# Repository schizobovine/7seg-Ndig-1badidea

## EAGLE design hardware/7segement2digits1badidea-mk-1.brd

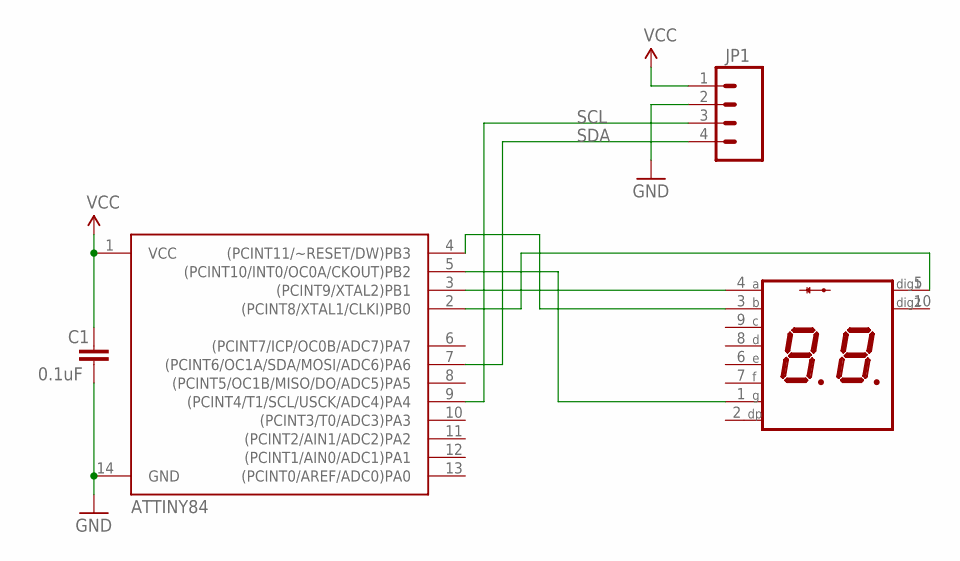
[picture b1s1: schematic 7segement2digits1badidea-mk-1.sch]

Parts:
C1: 0.1uF; CAP-PTH-SMALL
JP1: M04PTH; 1X04
U$1: 7SEG_2DIG_CA; 7SEG_2DIG_FUCKYOU
U$2: ATTINY84; SO14

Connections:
GND: C1.2, JP1.2, U$2.14 (GND)
unnamed: U$1.5 (DIG1), U$2.2 ((PCINT8/XTAL1/CLKI)PB0)
unnamed: U$1.4 (A), U$2.3 ((PCINT9/XTAL2)PB1)
unnamed: U$1.3 (B), U$2.4 ((PCINT11/~RESET/DW)PB3)
unnamed: U$1.1 (G), U$2.5 ((PCINT10/INT0/OC0A/CKOUT)PB2)
SCL: JP1.3, U$2.9 ((PCINT4/T1/SCL/USCK/ADC4)PA4)
SDA: JP1.4, U$2.7 ((PCINT6/OC1A/SDA/MOSI/ADC6)PA6)
VCC: C1.1, JP1.1, U$2.1 (VCC)

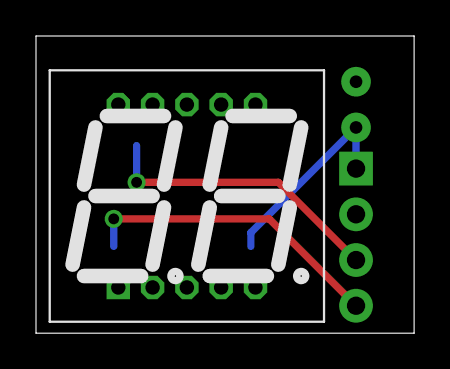
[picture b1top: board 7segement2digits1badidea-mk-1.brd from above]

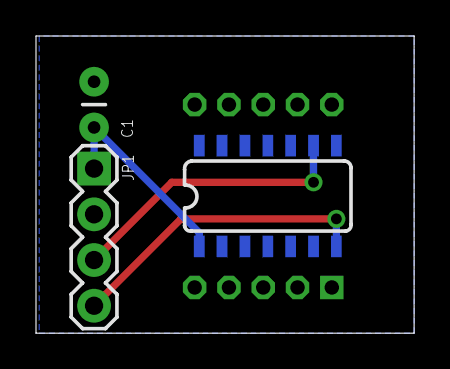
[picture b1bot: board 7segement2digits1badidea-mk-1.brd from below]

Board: 2 copper layers, 21.0 x 16.5 mm, 4 parts (3 on the bottom side), 8 nets.

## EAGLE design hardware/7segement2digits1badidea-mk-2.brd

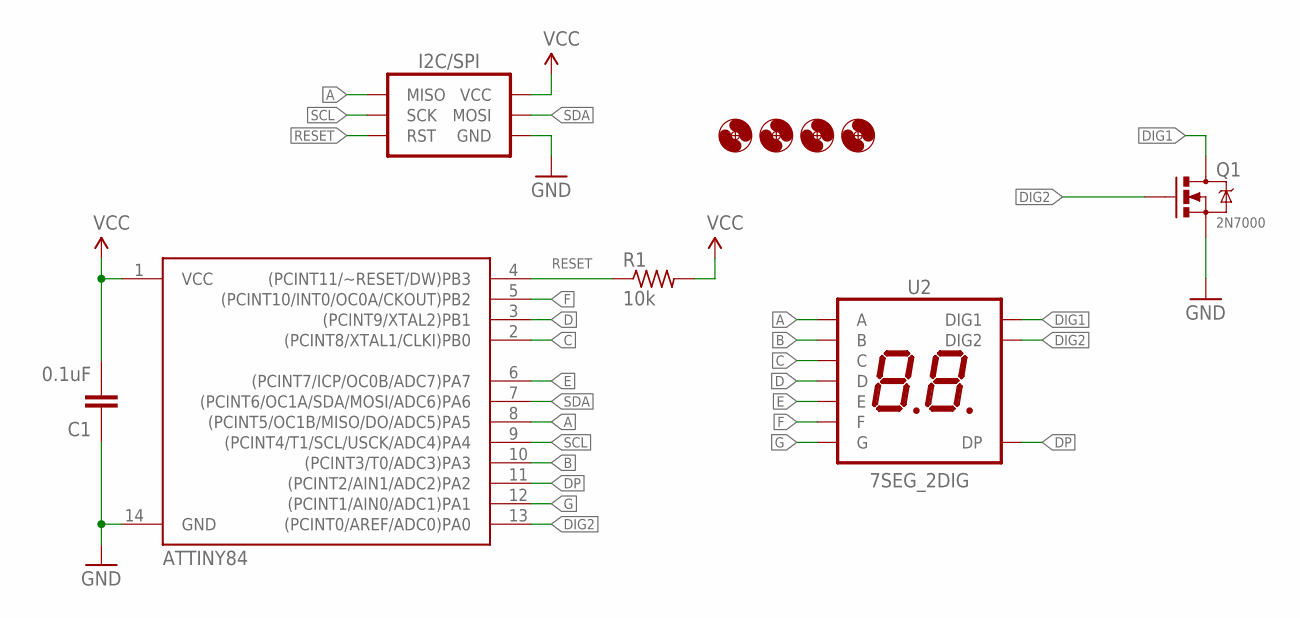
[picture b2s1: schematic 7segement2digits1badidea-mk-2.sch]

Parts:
C1: 0.1uF; C0805
H1, H2, H3, H4: HOLE#2; HOLE-#2
I2C/SPI: AVR_SPI_PRG_6PTH_INLINE_I2C; AVR_ISP_INLINE_PTH_I2C
Q1: 2N7000; SOT23
R1: 10k; R0805
U1: ATTINY84; SO14
U2: 7SEG_2DIG; 7SEG_2DIG_14MM

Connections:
A: I2C/SPI.MISO, U1.8 ((PCINT5/OC1B/MISO/DO/ADC5)PA5), U2.4 (A)
B: U1.10 ((PCINT3/T0/ADC3)PA3), U2.3 (B)
C: U1.2 ((PCINT8/XTAL1/CLKI)PB0), U2.9 (C)
D: U1.3 ((PCINT9/XTAL2)PB1), U2.8 (D)
DIG1: Q1.3 (D), U2.5 (DIG1)
DIG2: Q1.1 (G), U1.13 ((PCINT0/AREF/ADC0)PA0), U2.10 (DIG2)
DP: U1.11 ((PCINT2/AIN1/ADC2)PA2), U2.2 (DP)
E: U1.6 ((PCINT7/ICP/OC0B/ADC7)PA7), U2.6 (E)
F: U1.5 ((PCINT10/INT0/OC0A/CKOUT)PB2), U2.7 (F)
G: U1.12 ((PCINT1/AIN0/ADC1)PA1), U2.1 (G)
GND: C1.1, I2C/SPI.GND, Q1.2 (S), U1.14 (GND)
RESET: I2C/SPI.RESET (RST), R1.1, U1.4 ((PCINT11/~RESET/DW)PB3)
SCL: I2C/SPI.SCK, U1.9 ((PCINT4/T1/SCL/USCK/ADC4)PA4)
SDA: I2C/SPI.MOSI, U1.7 ((PCINT6/OC1A/SDA/MOSI/ADC6)PA6)
VCC: C1.2, I2C/SPI.VCC, R1.2, U1.1 (VCC)

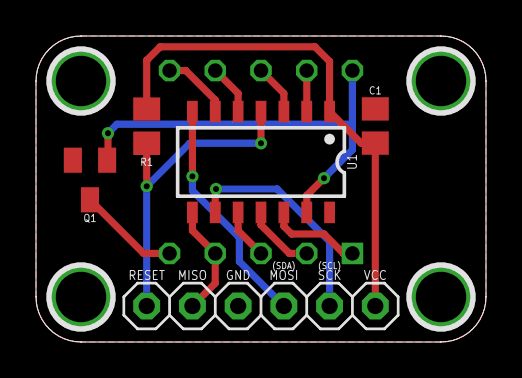
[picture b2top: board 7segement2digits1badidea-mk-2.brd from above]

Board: 2 copper layers, 25.0 x 17.0 mm, 10 parts (1 on the bottom side), 15 nets.

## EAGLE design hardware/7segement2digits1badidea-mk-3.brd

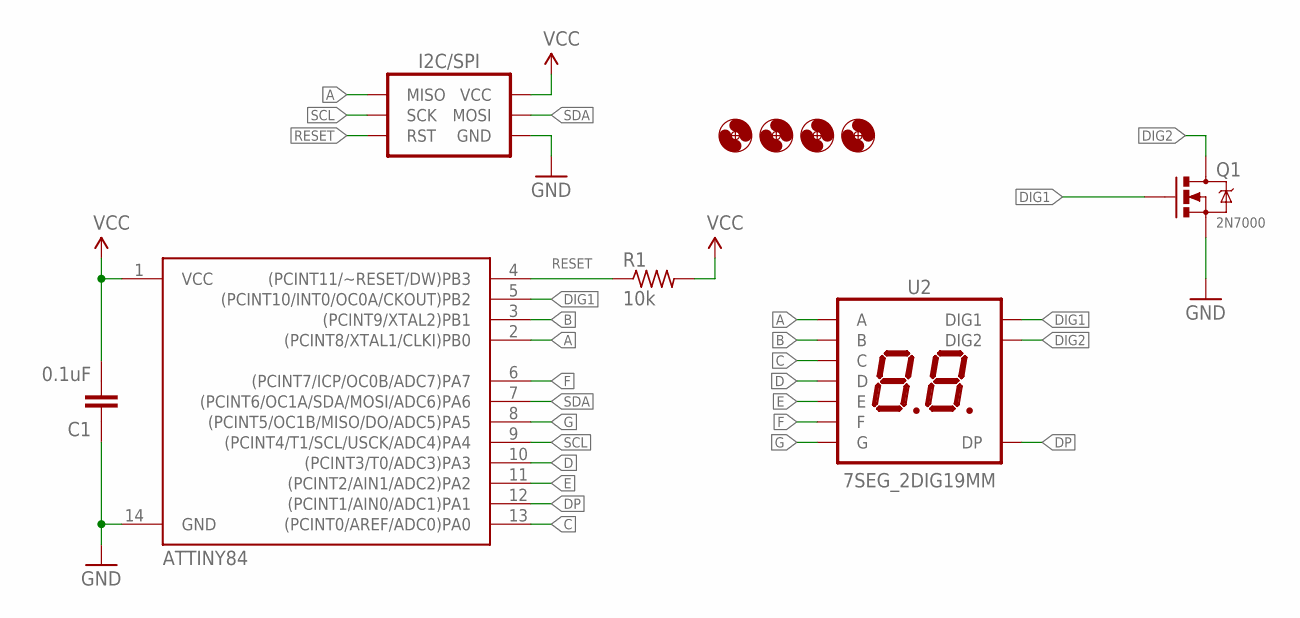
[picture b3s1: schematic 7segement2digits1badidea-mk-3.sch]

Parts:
C1: 0.1uF; C025-024X044
H1, H2, H3, H4: HOLE#2; HOLE-#2
I2C/SPI: AVR_SPI_PRG_6PTH_INLINE_I2C; AVR_ISP_INLINE_PTH_I2C
Q1: 2N7000; TO-92-AMMO
R1: 10k; RESISTOR-AXIAL-PTH-7.68MM
U1: ATTINY84; DIL14
U2: 7SEG_2DIG19MM; 7SEG_2DIG_19MM

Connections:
A: I2C/SPI.MISO, U1.2 ((PCINT8/XTAL1/CLKI)PB0), U2.10 (A)
B: U1.3 ((PCINT9/XTAL2)PB1), U2.9 (B)
C: U1.13 ((PCINT0/AREF/ADC0)PA0), U2.1 (C)
D: U1.10 ((PCINT3/T0/ADC3)PA3), U2.4 (D)
DIG1: Q1.2 (G), U1.5 ((PCINT10/INT0/OC0A/CKOUT)PB2), U2.8 (DIG1)
DIG2: Q1.3 (D), U2.7 (DIG2)
DP: U1.12 ((PCINT1/AIN0/ADC1)PA1), U2.2 (DP)
E: U1.11 ((PCINT2/AIN1/ADC2)PA2), U2.3 (E)
F: U1.6 ((PCINT7/ICP/OC0B/ADC7)PA7), U2.6 (F)
G: U1.8 ((PCINT5/OC1B/MISO/DO/ADC5)PA5), U2.5 (G)
GND: C1.1, I2C/SPI.GND, Q1.1 (S), U1.14 (GND)
RESET: I2C/SPI.RESET (RST), R1.P$1 (1), U1.4 ((PCINT11/~RESET/DW)PB3)
SCL: I2C/SPI.SCK, U1.9 ((PCINT4/T1/SCL/USCK/ADC4)PA4)
SDA: I2C/SPI.MOSI, U1.7 ((PCINT6/OC1A/SDA/MOSI/ADC6)PA6)
VCC: C1.2, I2C/SPI.VCC, R1.P$2 (2), U1.1 (VCC)

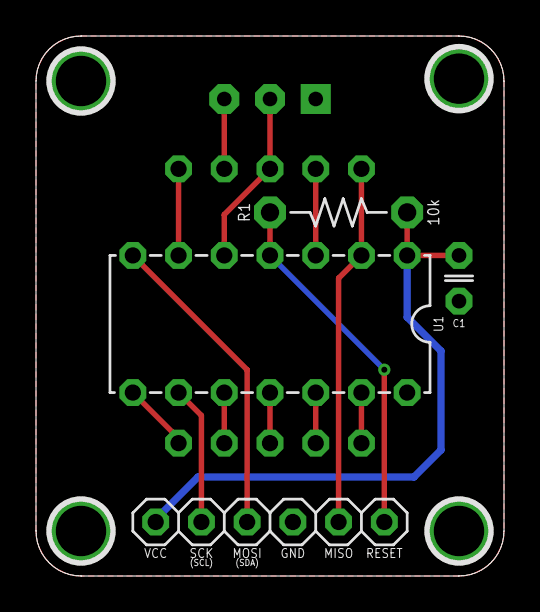
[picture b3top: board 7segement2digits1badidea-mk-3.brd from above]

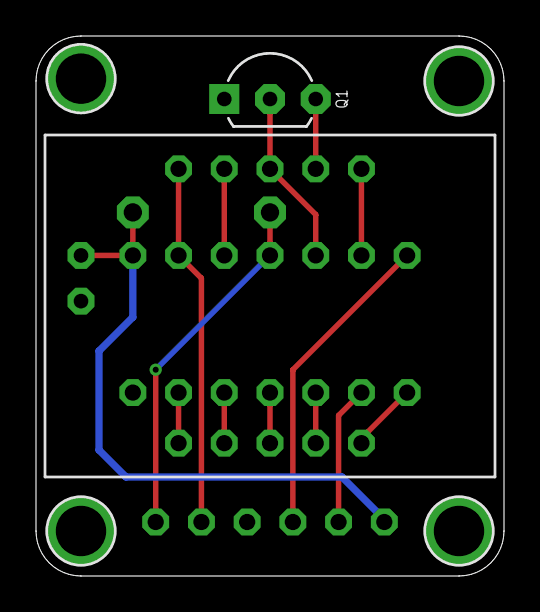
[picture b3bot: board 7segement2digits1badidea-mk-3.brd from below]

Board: 2 copper layers, 26.0 x 30.0 mm, 10 parts (2 on the bottom side), 15 nets.

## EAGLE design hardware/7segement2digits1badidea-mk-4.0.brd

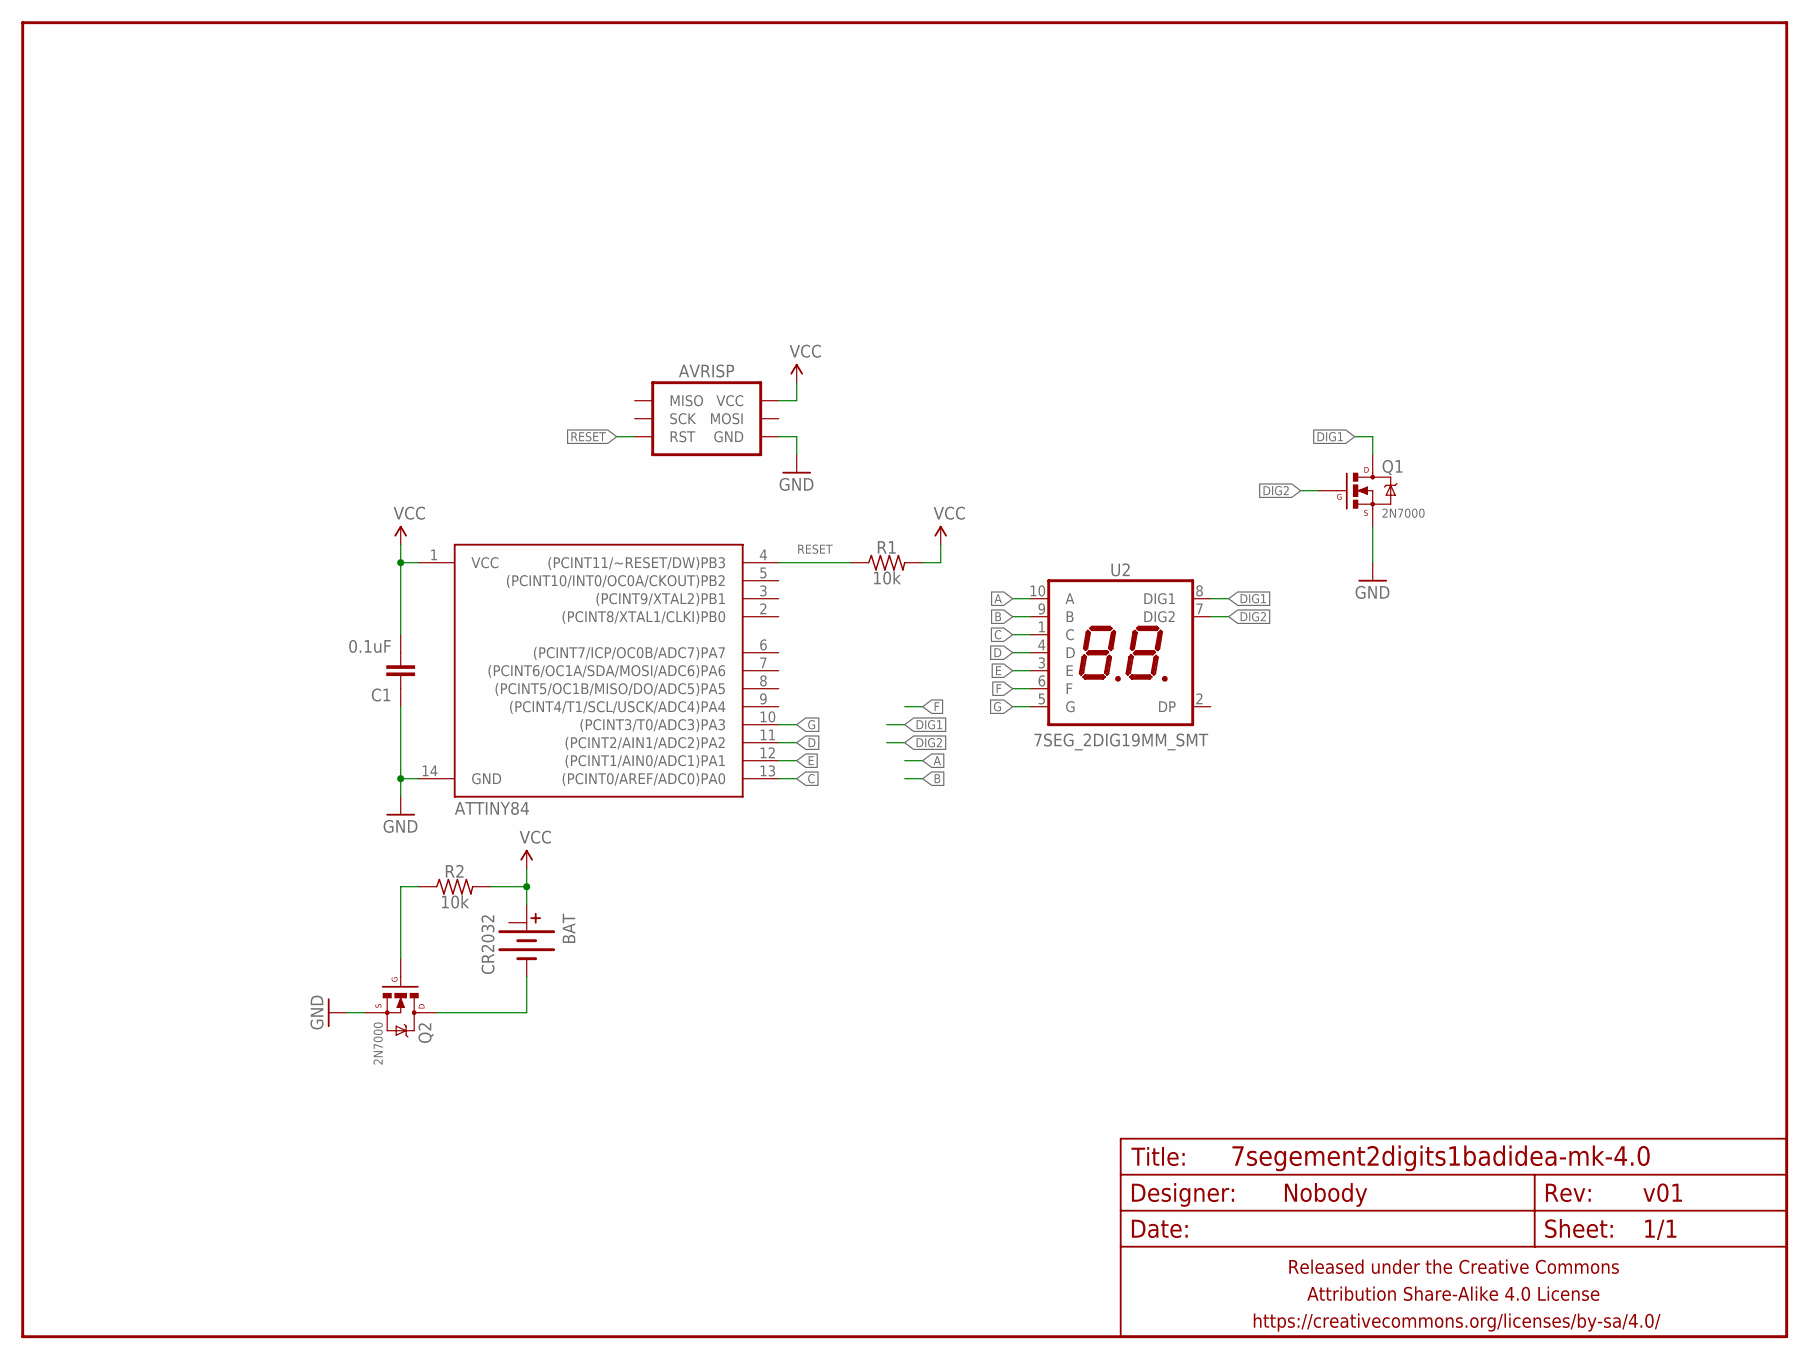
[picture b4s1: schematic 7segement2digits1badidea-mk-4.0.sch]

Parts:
AVRISP: AVR_SPI_PRG_6PTH; 2X3
BAT: CR2032; BATTCON_20MM_MINE_STAHPIT
C1: 0.1uF; C0805
FRAME1: FRAME-LETTERNO_PACKAGE; DUMMY
Q1, Q2: 2N7000; SOT23
R1, R2: 10k; R0805
U1: ATTINY84; SO14
U2: 7SEG_2DIG19MM_SMT; 7SEG_2DIG_19MM_SMT

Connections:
A: U2.10 (A)
B: U2.9 (B)
C: U1.13 ((PCINT0/AREF/ADC0)PA0), U2.1 (C)
D: U1.11 ((PCINT2/AIN1/ADC2)PA2), U2.4 (D)
DIG1: Q1.3 (D), U2.8 (DIG1)
DIG2: Q1.1 (G), U2.7 (DIG2)
E: U1.12 ((PCINT1/AIN0/ADC1)PA1), U2.3 (E)
F: U2.6 (F)
G: U1.10 ((PCINT3/T0/ADC3)PA3), U2.5 (G)
GND: AVRISP.6 (GND), C1.1, Q1.2 (S), Q2.2 (S), U1.14 (GND)
unnamed: Q2.1 (G), R2.1
unnamed: BAT.BOTTOM (-), Q2.3 (D)
RESET: AVRISP.5 (RST), R1.1, U1.4 ((PCINT11/~RESET/DW)PB3)
VCC: AVRISP.2 (VCC), BAT.TOP@1 (+), C1.2, R1.2, R2.2, U1.1 (VCC)

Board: 2 copper layers, 10 parts (1 on the bottom side), 11 nets, no tracks yet.

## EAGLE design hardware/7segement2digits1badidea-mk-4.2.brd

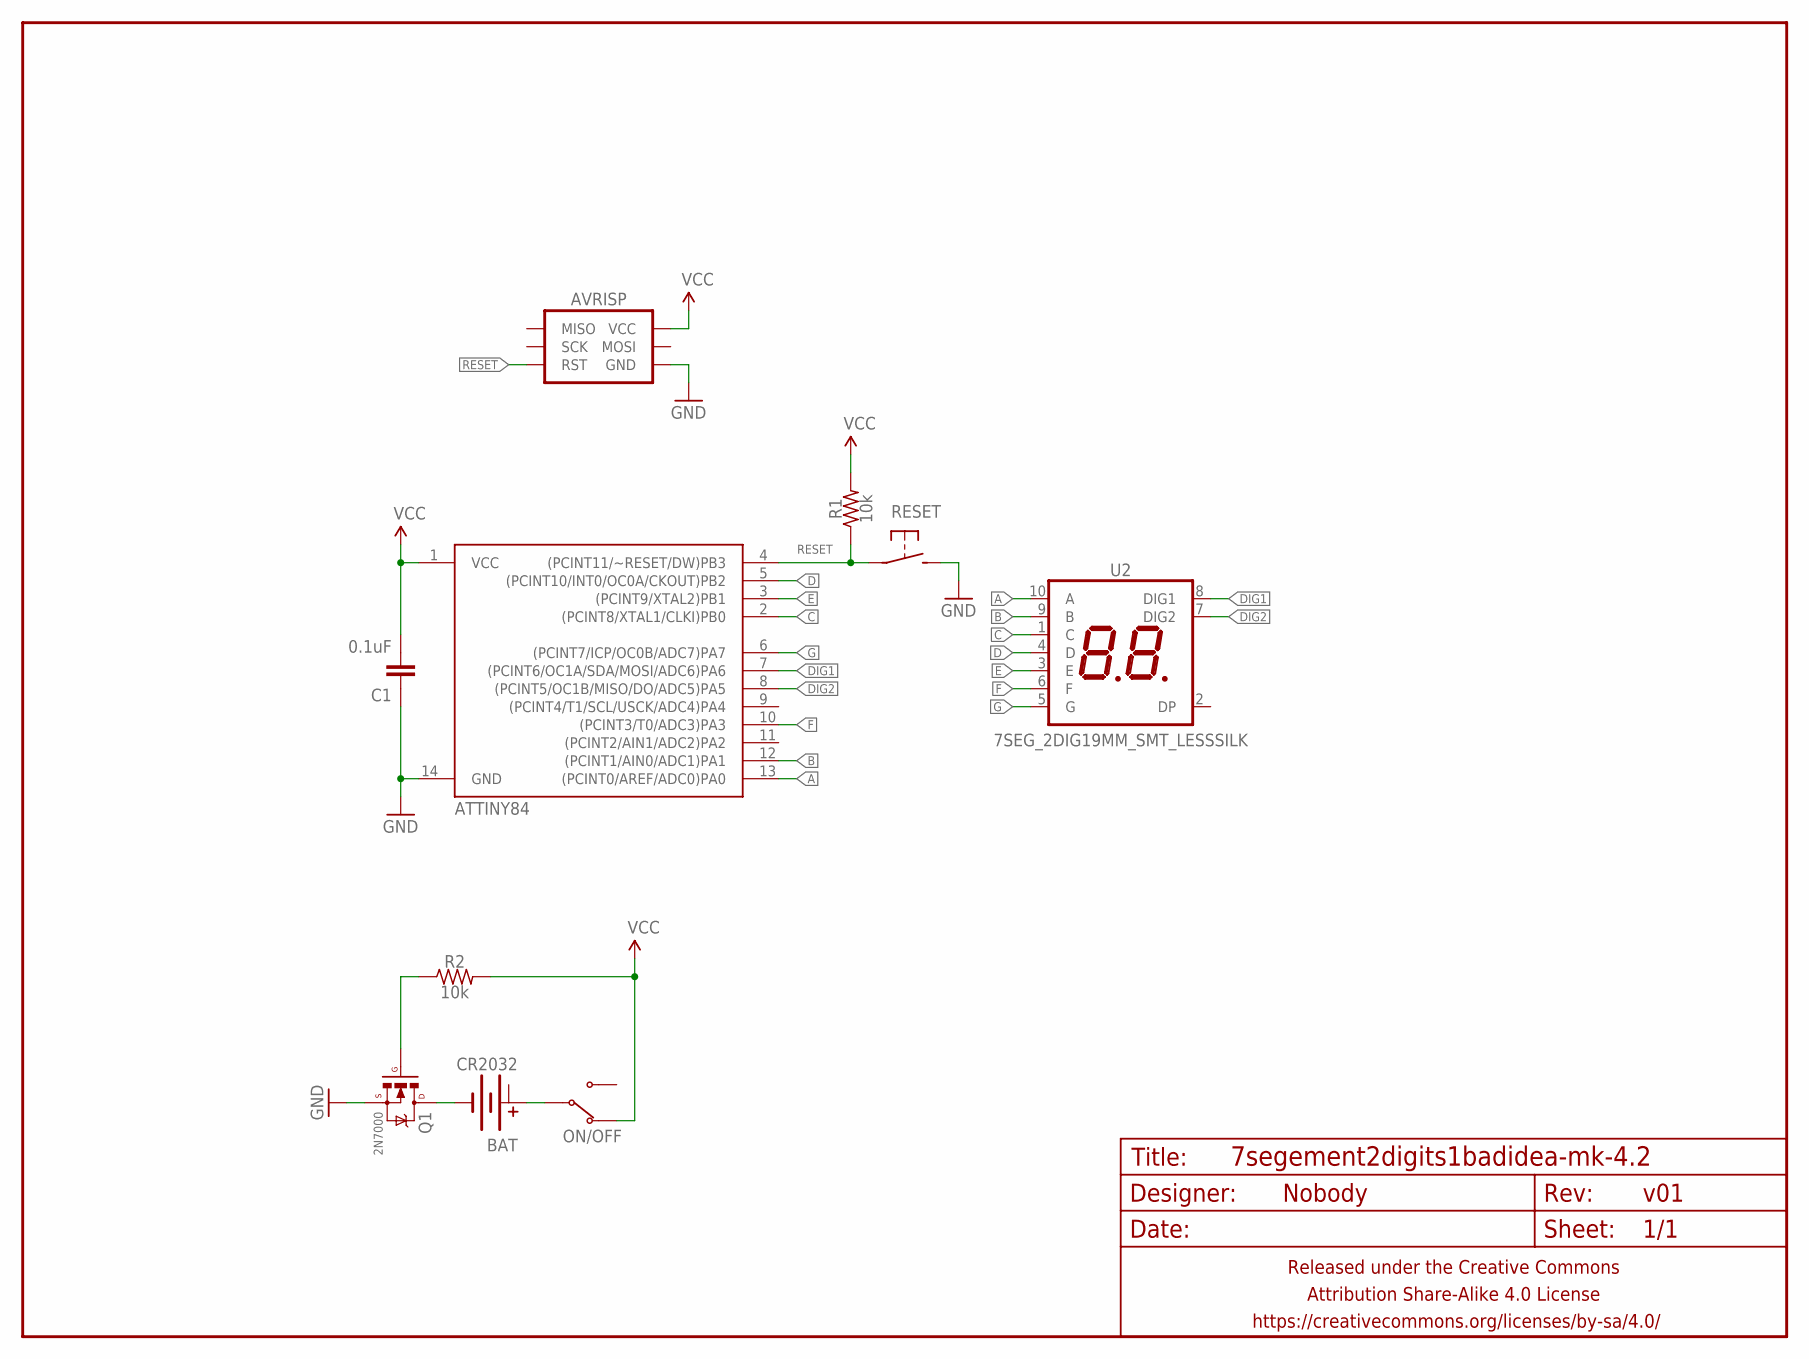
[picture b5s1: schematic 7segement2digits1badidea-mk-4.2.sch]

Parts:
AVRISP: AVR_SPI_PRG_6PTH; 2X3
BAT: CR2032; BATTCON_20MM_MINE_STAHPIT
C1: 0.1uF; C0805
FRAME1: FRAME-LETTERNO_PACKAGE; DUMMY
ON/OFF: SWITCH-SPDTPTH-RA-2.54MM; SPDT-RA-2.54MM
Q1: 2N7000; SOT23
R1, R2: 10k; R0805
RESET: SPST-NO-TACT3MM-RA; TACTILE-PTH-SIDE
U1: ATTINY84; SO14
U2: 7SEG_2DIG19MM_SMT_LESSSILK; 7SEG_2DIG_19MM_SMT_LESSSILK

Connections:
A: U1.13 ((PCINT0/AREF/ADC0)PA0), U2.10 (A)
B: U1.12 ((PCINT1/AIN0/ADC1)PA1), U2.9 (B)
C: U1.2 ((PCINT8/XTAL1/CLKI)PB0), U2.1 (C)
D: U1.5 ((PCINT10/INT0/OC0A/CKOUT)PB2), U2.4 (D)
DIG1: U1.7 ((PCINT6/OC1A/SDA/MOSI/ADC6)PA6), U2.8 (DIG1)
DIG2: U1.8 ((PCINT5/OC1B/MISO/DO/ADC5)PA5), U2.7 (DIG2)
E: U1.3 ((PCINT9/XTAL2)PB1), U2.3 (E)
F: U1.10 ((PCINT3/T0/ADC3)PA3), U2.6 (F)
G: U1.6 ((PCINT7/ICP/OC0B/ADC7)PA7), U2.5 (G)
GND: AVRISP.6 (GND), C1.1, Q1.2 (S), RESET.2, U1.14 (GND)
unnamed: Q1.1 (G), R2.1
unnamed: BAT.BOTTOM (-), Q1.3 (D)
unnamed: BAT.TOP@1 (+), ON/OFF.2 (COM)
RESET: AVRISP.5 (RST), R1.1, RESET.1, U1.4 ((PCINT11/~RESET/DW)PB3)
VCC: AVRISP.2 (VCC), C1.2, ON/OFF.1 (NC), R1.2, R2.2, U1.1 (VCC)

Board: 2 copper layers, 11 parts (4 on the bottom side), 15 nets, no tracks yet.

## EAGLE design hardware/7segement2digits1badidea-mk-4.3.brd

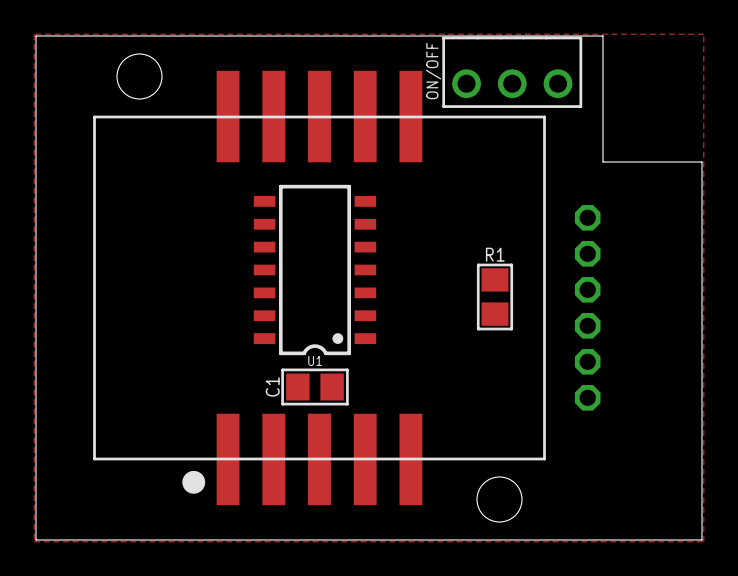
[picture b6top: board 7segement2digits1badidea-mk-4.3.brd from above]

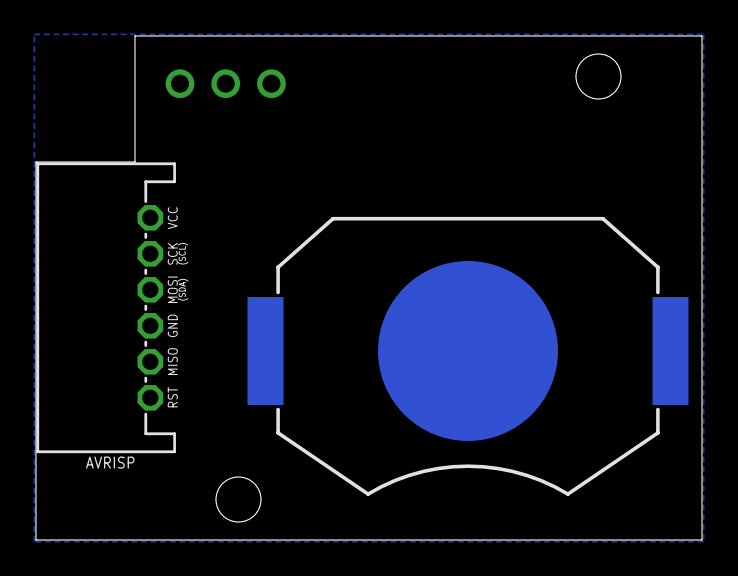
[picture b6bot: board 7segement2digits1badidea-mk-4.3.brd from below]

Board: 2 copper layers, 37.0 x 28.0 mm, 8 parts (2 on the bottom side), 6 nets, no tracks yet.

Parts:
AVRISP: AVR_SPI_PRG_6AVR-JST-PTH-RA-I2C; AVR-JST-6-PTH-RA-I2C
BAT1: CR2032; BATTCON_20MM_MINE_STAHPIT
C1: 0.1uF; C0805
FRAME1: FRAME-LETTERNO_PACKAGE; DUMMY
ON/OFF: SWITCH-SPDTPTH-RA-2.54MM; SPDT-RA-2.54MM
R1: 10k; R0805
U1: ATTINY84; SO14
U2: 7SEG_2DIG19MM_SMT_LESSSILK; 7SEG_2DIG_19MM_SMT_LESSSILK

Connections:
DIG1: U1.6, U2.8
DIG2: U1.5, U2.7
GND: AVRISP.GND, BAT1.BOTTOM, C1.1, U1.14
unnamed: BAT1.TOP@1, BAT1.TOP@2, ON/OFF.1
RESET: AVRISP.RESET, R1.1, U1.4
VCC: AVRISP.VCC, C1.2, ON/OFF.2, R1.2, U1.1

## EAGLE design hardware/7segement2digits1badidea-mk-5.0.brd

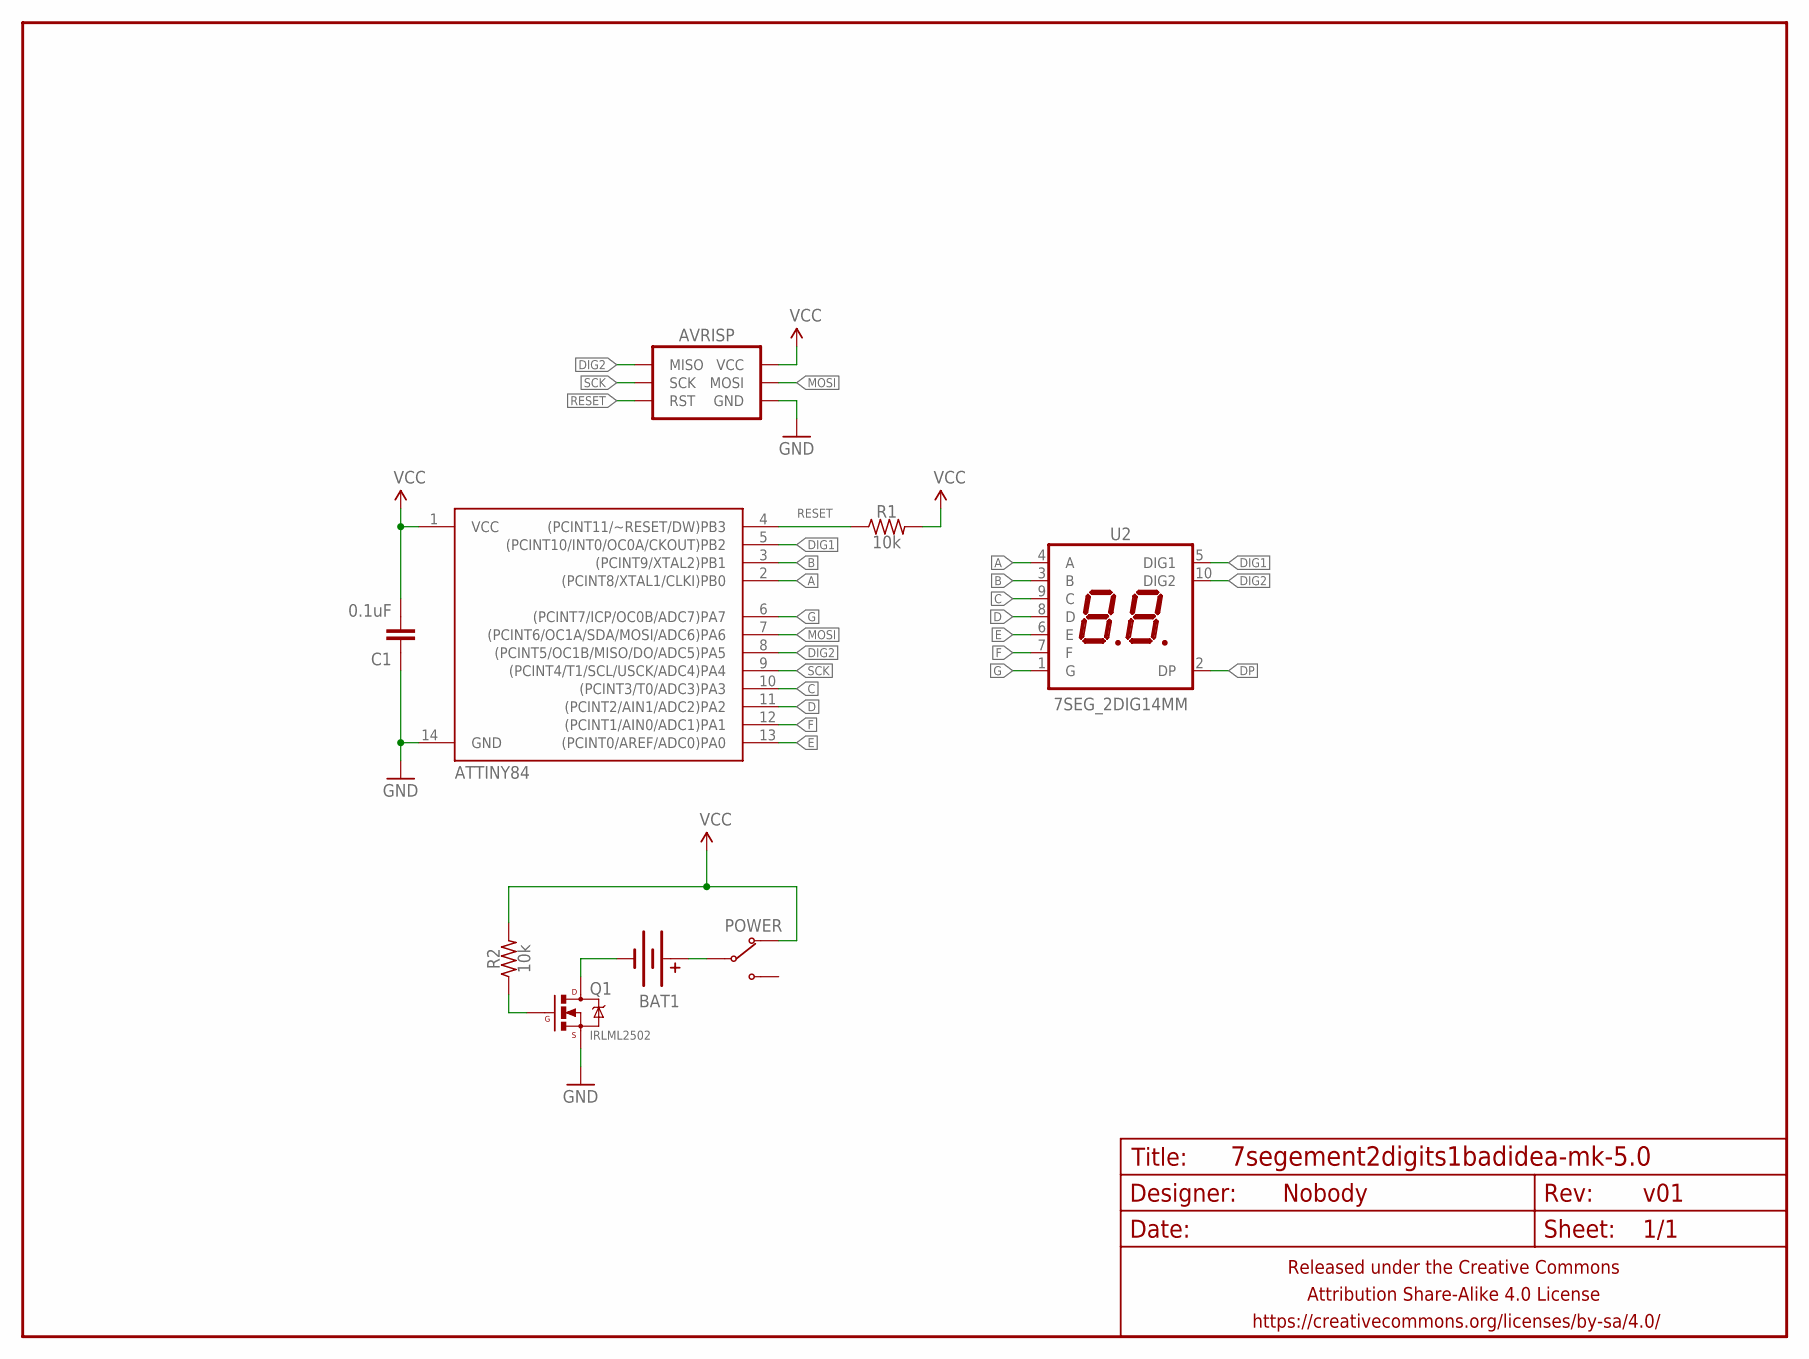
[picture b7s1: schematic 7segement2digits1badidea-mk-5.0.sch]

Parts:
AVRISP: AVR_SPI_PRG_6PTH; 2X3
BAT1: BATTERY20PTH_TOPLOAD; BATTCON_20MM_PTH_TOPLOAD
C1: 0.1uF; C0805
FRAME1: FRAME-LETTERNO_PACKAGE; DUMMY
POWER: SWITCH-SPDTPTH-RA-2.54MM; SPDT-RA-2.54MM
Q1: IRLML2502; SOT23
R1, R2: 10k; R0805
U1: ATTINY84; SO14
U2: 7SEG_2DIG14MM; 7SEG_2DIG_14MM

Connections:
A: U1.2 ((PCINT8/XTAL1/CLKI)PB0), U2.4 (A)
B: U1.3 ((PCINT9/XTAL2)PB1), U2.3 (B)
C: U1.10 ((PCINT3/T0/ADC3)PA3), U2.9 (C)
D: U1.11 ((PCINT2/AIN1/ADC2)PA2), U2.8 (D)
DIG1: U1.5 ((PCINT10/INT0/OC0A/CKOUT)PB2), U2.5 (DIG1)
DIG2: AVRISP.1 (MISO), U1.8 ((PCINT5/OC1B/MISO/DO/ADC5)PA5), U2.10 (DIG2)
DP: U2.2 (DP)
E: U1.13 ((PCINT0/AREF/ADC0)PA0), U2.6 (E)
F: U1.12 ((PCINT1/AIN0/ADC1)PA1), U2.7 (F)
G: U1.6 ((PCINT7/ICP/OC0B/ADC7)PA7), U2.1 (G)
GND: AVRISP.6 (GND), C1.1, Q1.2 (S), U1.14 (GND)
MOSI: AVRISP.4 (MOSI), U1.7 ((PCINT6/OC1A/SDA/MOSI/ADC6)PA6)
unnamed: BAT1.+, POWER.2 (COM)
unnamed: BAT1.-, Q1.3 (D)
unnamed: Q1.1 (G), R2.1
RESET: AVRISP.5 (RST), R1.1, U1.4 ((PCINT11/~RESET/DW)PB3)
SCK: AVRISP.3 (SCK), U1.9 ((PCINT4/T1/SCL/USCK/ADC4)PA4)
VCC: AVRISP.2 (VCC), C1.2, POWER.1 (NC), R1.2, R2.2, U1.1 (VCC)

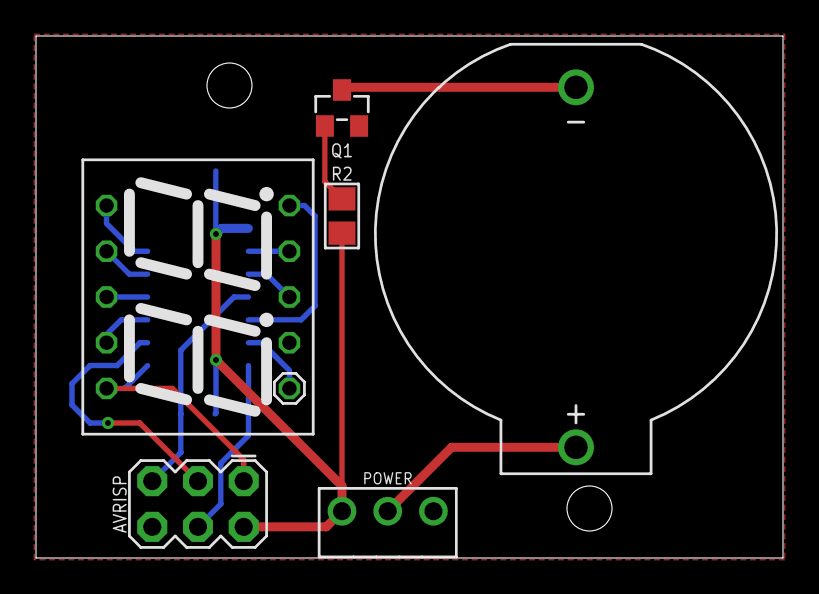
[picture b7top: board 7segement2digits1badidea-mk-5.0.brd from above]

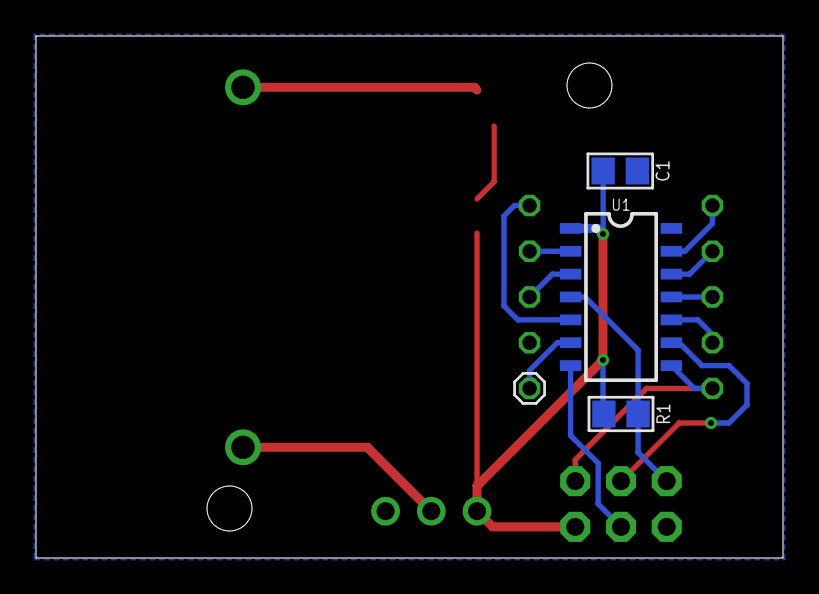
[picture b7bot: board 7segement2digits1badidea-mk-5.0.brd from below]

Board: 2 copper layers, 41.5 x 29.0 mm, 10 parts (3 on the bottom side), 17 nets.

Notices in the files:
parts and their libraries:
SparkFun-DigitalIC: Licensing: Creative Commons ShareAlike 4.0 International - https://creativecommons.org/licenses/by-sa/4.0
A_butts: Released under the Creative Commons Attribution Share-Alike 4.0 License
A_butts: https://creativecommons.org/licenses/by-sa/4.0
